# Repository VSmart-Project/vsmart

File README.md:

# Vsmart — Cloud-based Vehicle GPS Tracking and Management System (IoT)

> **Graduation Project** — Real-time GPS Tracking, Geofencing, Anti-theft protection, and instant intrusion alerts system, built entirely on AWS Serverless Cloud Architecture.

## Quick local start

From the `DATN` directory, start the configured local services with:

```bash
./start-system.sh
```

The script starts the backend (port 3001) and web dashboard (port 5173) by default.
Pass `--with-mobile` if you want to start the Expo mobile app as well.
Use `./start-system.sh --help` to view all available options. Press `Ctrl+C` or run `./stop-system.sh`
to stop all running services. Service logs are retained under `.runtime/logs/`.

---

## Table of Contents

1. [Project Overview](#1-project-overview)
2. [Source Code Directory Structure](#2-source-code-directory-structure)
3. [System Architecture](#3-system-architecture)
4. [AWS Services Utilized](#4-aws-services-utilized)
5. [System Workflows](#5-system-workflows)
6. [Deployment Guide](#6-deployment-guide)
   - [Step 1: System Prerequisites](#step-1-system-prerequisites)
   - [Step 2: Deploy AWS Infrastructure](#step-2-deploy-aws-infrastructure)
   - [Step 3: Configure & Run Backend](#step-3-configure--run-backend)
   - [Step 4: Configure & Run Frontend Web Dashboard](#step-4-configure--run-frontend-web-dashboard)
   - [Step 5: Configure & Run Mobile App](#step-5-configure--run-mobile-app)
   - [Step 6: GPS Simulation & End-to-End Testing](#step-6-gps-simulation--end-to-end-testing)
7. [API Reference](#7-api-reference)
8. [Troubleshooting & FAQ](#8-troubleshooting--faq)
9. [Local-First & ngrok Webhook Workflow](#9-local-first--ngrok-webhook-workflow)
10. [Technology Stack](#10-technology-stack)
11. [References](#11-references)

---

## 1. Project Overview

### Problem Statement

Traditional fleet management systems usually require dedicated physical servers, resulting in high operational costs, maintenance overhead, and poor scalability. The **Vsmart** project solves these issues by leveraging a modern **Serverless Event-Driven Architecture** on AWS, eliminating server management while ensuring high availability, lower latency, and pay-as-you-go cost-efficiency.

### Key Features

| Feature | Description |
|---|---|
| **Real-time GPS Tracking** | Visualizes live vehicle locations on high-performance vector maps |
| **Geofencing** | Custom virtual boundaries (Polygon/Circle) with instant entrance/exit notifications |
| **Anti-theft Security** | Automatic 2-meter radius geofencing around parked vehicles with instant push/email alerts on breach |
| **Multi-platform** | Synchronized Web Dashboard (React) + Mobile App (React Native/Expo) |
| **Identity & Authentication** | Secure user registration/sign-in using Amazon Cognito + JWT verification |
| **Position History** | Replays past vehicle travel routes along a timeline with detailed logs |
| **Serverless & Scalable** | Entire pipeline scale dynamically based on ingestion load, keeping maintenance near zero |
| **Infrastructure as Code (IaC)** | Deploys 30+ AWS resources using a single command via AWS CloudFormation/SAM |

---

## 2. Source Code Directory Structure

The project is structured into **4 independent modules**, enabling isolated development and deployment:

```
7-DATN/
│
├── vsmart-infrastructure/   ← AWS Serverless Infrastructure (IaC)
│   ├── template.yml                             # Primary SAM Template (30+ AWS resources)
│   ├── packaged.yml                             # Packaged Template containing S3 URIs
│   └── lambda/                                  # Serverless Functions (Python 3.12)
│       ├── iot-message-processor/               #   → Parses MQTT packets & updates ALS Tracker
│       ├── geofence-event-consumer/             #   → Processes Geofence breach events from SQS
│       ├── realtime-event-publisher/            #   → Publishes real-time events to clients via IoT Core
│       └── offline-detector/                    #   → Cron job identifying offline devices (every 1min)
│
├── vsmart-backend/          ← Node.js REST API & Socket.io Proxy
│   ├── index.js                                 # Entry point (Express server & Socket.io, port 3001)
│   ├── src/
│   │   ├── config/
│   │   │   ├── aws.js                           #   AWS SDK clients configuration
│   │   │   ├── constants.js                     #   Global constants & thresholds
│   │   │   ├── realtime.js                      #   Real-time telemetry flags
│   │   │   ├── realtimeEventSchema.js           #   Real-time event validations
│   │   │   └── swagger.js                       #   Swagger/OpenAPI UI config
│   │   ├── controllers/
│   │   │   ├── deviceController.js              #   CRUD operations & location metadata merging
│   │   │   ├── authController.js                #   Cognito user auth controller
│   │   │   └── antitheftController.js           #   Anti-theft activation and status
│   │   ├── routes/
│   │   │   ├── devices.js                       #   /api/devices endpoints
│   │   │   ├── auth.js                          #   /api/auth endpoints
│   │   │   └── antitheft.js                     #   /api/antitheft endpoints
│   │   ├── services/
│   │   │   ├── dynamoService.js                 #   DynamoDB wrapper
│   │   │   ├── locationService.js               #   Amazon Location Service wrapper
│   │   │   ├── snsService.js                    #   SNS SMS/Email notifications
│   │   │   ├── antitheftWorker.js               #   Parked vehicle monitor thread (15s interval)
│   │   │   └── geoUtils.js                      #   Distance calculations (Turf.js)
│   │   └── middleware/
│   │       ├── auth.js                          #   Cognito ID Token JWT verifier
│   │       └── errorHandler.js                  #   Global error catcher
│   └── scripts/
│       ├── interactive-move.js                  #   Interactive GPS Simulator (MQTT → IoT Core)
│       ├── move-device.js                       #   Single device route simulator
│       └── backfill-device-owners.js            #   Owner backfill utility script
│
├── vsmart-web/             ← Web Client (React 19 + Vite 8)
│   ├── index.html                               # HTML Entry
│   ├── vite.config.js                           # Vite bundler config (port 5173)
│   ├── tailwind.config.js                       # TailwindCSS styles configuration
│   └── src/
│       ├── App.jsx                              # Router, auth checks, and Socket.io client
│       ├── configuration.js                     # Local AWS config mapping
│       ├── components/
│       │   ├── auth/                            #   Sign-in, sign-up, and confirmation forms
│       │   ├── map/                             #   MapLibre GL map view & draw controllers
│       │   ├── devices/                         #   Vehicle list, details, and forms
│       │   ├── geofences/                       #   Geofencing controls & drawers
│       │   └── layout/                          #   Sidebar and Header layouts
│       ├── hooks/                               #   Custom React hooks (useDeviceManager, etc.)
│       ├── api/                                 #   Fetch-based REST client
│       └── utils/                               #   AWS Identity Pool credentials resolver
│
└── vsmart-mobile/                               ← Mobile Client (React Native + Expo SDK 54)
    ├── app.json                                 # Expo configuration file
    ├── app/                                     # File-based navigation screens
    │   ├── _layout.jsx                          #   Root provider layout
    │   ├── login.jsx                            #   Login screen
    │   ├── onboarding.jsx                       #   Onboarding flow
    │   ├── map.jsx                              #   Full screen map tracking view
    │   ├── scan.jsx                             #   Camera QR/Barcode scanner
    │   └── (tabs)/                              #   Tab navigator (Home, Devices, Settings)
    └── src/
        ├── configuration.js                     #   Mobile AWS configuration constants
        ├── contexts/                            #   Global contexts (DeviceDataContext, etc.)
        └── utils/                               #   Cognito authentication & AWS SDK helpers
```

---

## 3. System Architecture

The system utilizes an **Event-Driven Serverless Ingestion Pipeline** on AWS coupled with a **Node.js WebSockets Proxy** to handle live telemetry feeds with millisecond latency:

```mermaid
%%{init: {'theme': 'base', 'themeVariables': { 'fontFamily': 'Inter, sans-serif', 'fontSize': '13px', 'primaryColor': '#4f46e5', 'primaryTextColor': '#ffffff', 'primaryBorderColor': '#4338ca', 'lineColor': '#64748b', 'secondaryColor': '#f8fafc', 'tertiaryColor': '#ffffff' }}}%%
graph TB
    subgraph Clients ["Client Applications"]
        Web["Web Dashboard (React + Vite)"]
        Mobile["Mobile App (React Native + Expo)"]
    end

    subgraph Backend ["Backend Proxy (Node.js & Express)"]
        Express["Express Server (Port 3001)"]
        SocketServer["Socket.io Server (WebSocket Broker)"]
        AntitheftWorker["Anti-theft Worker (Interval: 15s)"]
    end

    subgraph AWSCloud ["AWS Serverless Cloud Infrastructure"]
        IoTCore["AWS IoT Core (MQTT Broker)"]
        LambdaIngest["Lambda: IoTMessageProcessor"]
        LambdaGeofence["Lambda: GeofenceEventConsumer"]
        LambdaOffline["Lambda: OfflineDetector (Cron: 1min)"]
        
        subgraph Databases ["AWS Databases"]
            DynamoDevices[("DynamoDB: DevicesTable")]
            DynamoState[("DynamoDB: DeviceStateTable")]
        end
        
        subgraph LocationServices ["AWS Location Services"]
            ALSMap["Map: Vsmart-Map"]
            ALSTracker["Tracker: Vsmart-Tracker"]
            ALSCollection["Collection: GeofenceCollection"]
        end
        
        EventBridge["Amazon EventBridge"]
        SQSQueue["Amazon SQS (Geofence Alerts)"]
        SNSTopic["Amazon SNS (Email Alerts)"]
        Cognito["Amazon Cognito (User & Identity Pools)"]
    end

    %% Connections
    Web & Mobile <-->|"1. REST API Requests (Cognito JWT)"| Express
    Web & Mobile <-->|"2. Socket.io WebSockets"| SocketServer
    Web & Mobile -->|"3. Vector Map Tiles Fetch"| ALSMap
    Web & Mobile -->|"4. Credentials Exchange"| Cognito

    %% Ingestion
    Simulator["GPS Device / Simulator"] -->|"5. Publish Location (MQTT)"| IoTCore
    IoTCore -->|"6. Trigger Rule"| LambdaIngest
    
    LambdaIngest -->|"7a. Log coordinate history"| ALSTracker
    LambdaIngest -->|"7b. Save latest state"| DynamoState
    LambdaIngest -->|"7c. HTTP POST Webhook"| Express
    
    %% Geofence Transitions
    ALSTracker -->|"8. Evaluate transitions"| ALSCollection
    ALSCollection -->|"9. ENTER/EXIT Event"| EventBridge
    EventBridge -->|"10. Queue message"| SQSQueue
    SQSQueue -->|"11. Poll batch"| LambdaGeofence
    LambdaGeofence -->|"12. HTTP POST Webhook (Alert)"| Express

    %% Anti-theft Guard
    AntitheftWorker -->|"13. Query coordinates"| DynamoState & ALSTracker
    AntitheftWorker -->|"14. Trigger Alert (Breach)"| SNSTopic

    %% Cron Tasks
    EventBridge -->|"15. Trigger Cron"| LambdaOffline
    LambdaOffline -->|"16. Mark Offline (>120s)"| DynamoState
    LambdaOffline -->|"17. HTTP POST Webhook (Status)"| Express

    %% Webhook forwarding to sockets
    Express -->|"18. Forward event payload"| SocketServer

    %% Styling classes
    style Web fill:#e0f2fe,stroke:#38bdf8,stroke-width:2px,color:#0f172a
    style Mobile fill:#e0f2fe,stroke:#38bdf8,stroke-width:2px,color:#0f172a
    style Express fill:#faf5ff,stroke:#c084fc,stroke-width:2px,color:#0f172a
    style SocketServer fill:#faf5ff,stroke:#c084fc,stroke-width:2px,color:#0f172a
    style AntitheftWorker fill:#faf5ff,stroke:#c084fc,stroke-width:2px,color:#0f172a
    style IoTCore fill:#fff7ed,stroke:#fdba74,stroke-width:2px,color:#0f172a
    style LambdaIngest fill:#fff7ed,stroke:#fdba74,stroke-width:2px,color:#0f172a
    style LambdaGeofence fill:#fff7ed,stroke:#fdba74,stroke-width:2px,color:#0f172a
    style LambdaOffline fill:#fff7ed,stroke:#fdba74,stroke-width:2px,color:#0f172a
    style EventBridge fill:#fff7ed,stroke:#fdba74,stroke-width:2px,color:#0f172a
    style SQSQueue fill:#fff7ed,stroke:#fdba74,stroke-width:2px,color:#0f172a
    style SNSTopic fill:#fff7ed,stroke:#fdba74,stroke-width:2px,color:#0f172a
    style Cognito fill:#fff7ed,stroke:#fdba74,stroke-width:2px,color:#0f172a
    style DynamoDevices fill:#f0fdf4,stroke:#86efac,stroke-width:2px,color:#0f172a
    style DynamoState fill:#f0fdf4,stroke:#86efac,stroke-width:2px,color:#0f172a
    style ALSMap fill:#f0fdfa,stroke:#5eead4,stroke-width:2px,color:#0f172a
    style ALSTracker fill:#f0fdfa,stroke:#5eead4,stroke-width:2px,color:#0f172a
    style ALSCollection fill:#f0fdfa,stroke:#5eead4,stroke-width:2px,color:#0f172a
```

### Architectural Design Principles

| Principle | Description |
|---|---|
| **Separation of Concerns** | Decouples IoT telemetry ingestion from application API layers to prevent system crashes on high device activity. |
| **Event-Driven & Serverless** | Coordinates flow automatically through EventBridge, SQS, and Lambda, providing cost-efficiency and horizontal scaling. |
| **Dual Data Pipeline** | Integrates low-cost NoSQL storage (DynamoDB for metadata) with specialized geo-caching databases (Amazon Location Tracker for spatial coordinates). |
| **WebSockets API Gateway Proxy** | Connects clients via lightweight Socket.io WebSockets instead of direct AWS MQTT. The backend exposes a secure `/api/realtime/event` webhook called by AWS Lambda. |
| **Cognito-Federated Identity** | Uses Amazon Cognito User Pools for authorization. The client exchanges JWT tokens for AWS temporary credentials via Cognito Identity Pools to read map vector tiles directly. |

---

## 4. AWS Services Utilized

### Core Services

| Service | Resource Name | Purpose |
|---|---|---|
| **Amazon Location Service** | `Vsmart-Map` | Renders map vector tiles (Esri Navigation style) |
| | `Vsmart-Tracker` | Caches coordinates history, applies `DistanceBased` filtering |
| | `Vsmart-GeofenceCollection` | Stores geofence boundary coordinates |
| **AWS IoT Core** | Rule: `UpdateLocationTracker` | Receives incoming MQTT telemetry and routes payload to Lambda |
| **Amazon DynamoDB** | `Vsmart-Devices` | Device profiles database (name, license plate, status) |
| | `Vsmart-DeviceState` | Live runtime state database (online flag, last seen timestamp, anti-theft trigger) |
| **Amazon Cognito** | `Vsmart-UserPool` | Secure registration and login gateway |

### Supporting Services

| Service | Resource Name | Purpose |
|---|---|---|
| **AWS Lambda** | `IoTMessageProcessor` | Validates telemetry ➔ updates location ➔ calls Backend Webhook |
| | `GeofenceEventConsumer` | Handles geofence breaches ➔ calls Backend Webhook |
| | `OfflineDetector` | Queries the online-state index and identifies offline vehicles (>120s) |
| **Amazon EventBridge** | `GeofenceEventRule` | Captures geofence breach notifications ➔ routes to SQS |
| | `OfflineDetectorSchedule` | Generates cron triggers every minute |
| **Amazon SQS** | `GeofenceEvents` | Queues geofence breach events for batch consumption |
| **Amazon SNS** | `AntitheftAlerts` | Dispatches warning emails to owners on anti-theft breaches |
| | `IoTErrors` | Emails administrators on processing failures |
| **CloudFormation** | `Vsmart-UnifiedStack` | Deploys the entire backend cloud infrastructure as code |

---

## 5. System Workflows

### A. Location Telemetry Pipeline — GPS → Cloud → Clients

Updates vehicle markers on the map within milliseconds of receiving a new GPS coordinate:

```mermaid
%%{init: {'theme': 'base', 'themeVariables': { 'fontFamily': 'Inter, sans-serif', 'fontSize': '12px', 'primaryColor': '#4f46e5', 'primaryTextColor': '#ffffff', 'lineColor': '#64748b' }}}%%
sequenceDiagram
    autonumber
    participant Device as 🛰️ GPS Device
    participant IoT as 📡 AWS IoT Core
    participant Ingest as ⚡ Lambda: IoTMessageProcessor
    participant ALS as 📍 AWS Location Tracker
    participant Dynamo as 🗄️ DynamoDB (DeviceState)
    participant Backend as 🔧 Backend Express
    participant WebSockets as 🔌 Socket.io Server
    participant UI as 💻 Client Map UI

    Device->>IoT: Publish MQTT payload (location topic)
    IoT->>Ingest: Trigger Lambda with payload
    activate Ingest
    Ingest->>ALS: batch_update_device_position(Coordinates)
    Ingest->>Dynamo: Update state (isOnline=true, lastSeenAt, coordinates)
    Ingest->>Backend: HTTP POST /api/realtime/event (with API Key)
    deactivate Ingest
    activate Backend
    Backend->>WebSockets: Emit 'realtime-event'
    deactivate Backend
    WebSockets-->>UI: Push position data via WebSocket connection
    UI->>UI: Re-render map marker dynamically (smooth translation)
```

---

### B. Device Registration & Retrieval Workflow

Fetches registered devices, resolving metadata and coordinates from distinct databases:

```mermaid
%%{init: {'theme': 'base', 'themeVariables': { 'fontFamily': 'Inter, sans-serif', 'fontSize': '12px', 'primaryColor': '#4f46e5', 'primaryTextColor': '#ffffff', 'lineColor': '#64748b' }}}%%
sequenceDiagram
    autonumber
    participant UI as 💻 Web/Mobile Client
    participant Backend as 🔧 Backend Express
    participant Cognito as 🔐 AWS Cognito
    participant Dynamo as 🗄️ DynamoDB (DevicesTable)
    participant ALS as 📍 AWS Location Tracker

    UI->>Backend: GET /api/devices (Header: Bearer JWT)
    activate Backend
    Backend->>Cognito: Verify JWT signature & expiry
    Cognito-->>Backend: Verification success
    Backend->>Dynamo: Scan/Query device metadata by ownerUserId
    Dynamo-->>Backend: Return metadata (name, plate, type, antitheft)
    Backend->>ALS: ListDevicePositions (Fetch last coordinates)
    ALS-->>Backend: Return positions & timestamps
    Backend->>Backend: Merge metadata & position by deviceId
    Backend->>Backend: Calculate isOnline (sampleTime < 2 mins)
    Backend-->>UI: Return JSON Response
    deactivate Backend
```

---

### C. Geofencing Warning Pipeline

Monitors boundary crossings and alerts clients in real-time:

```mermaid
%%{init: {'theme': 'base', 'themeVariables': { 'fontFamily': 'Inter, sans-serif', 'fontSize': '12px', 'primaryColor': '#4f46e5', 'primaryTextColor': '#ffffff', 'lineColor': '#64748b' }}}%%
sequenceDiagram
    autonumber
    participant UI as 💻 Web Dashboard
    participant Cognito as 🔐 Cognito Identity Pool
    participant ALS as 📍 AWS Location (GeofenceCollection)
    participant EventBridge as 📅 AWS EventBridge
    participant SQS as 📊 Amazon SQS Queue
    participant Consumer as ⚡ Lambda: GeofenceEventConsumer
    participant Backend as 🔧 Backend Express
    participant WebSockets as 🔌 Socket.io Server
    participant AlertUI as 📱 Client App (Toast/Notification)

    UI->>Cognito: Request temporary credentials
    Cognito-->>UI: Return Access & Secret Keys
    UI->>ALS: Direct PUT /geofences (GeoJSON Polygon/Circle)
    Note over ALS: ALS Tracker evaluates coordinates against Geofences
    ALS->>EventBridge: Publish event on ENTER/EXIT transition
    EventBridge->>SQS: Push event to Queue
    SQS->>Consumer: Trigger Lambda with batch of events
    activate Consumer
    Consumer->>Backend: HTTP POST /api/realtime/event (Alert payload)
    deactivate Consumer
    activate Backend
    Backend->>WebSockets: Broadcast alert to user's room
    deactivate Backend
    WebSockets-->>AlertUI: Push geofence alert event
    AlertUI->>AlertUI: Display Toast Alert & Play Alarm Sound
```

---

### D. Anti-theft Protection Workflow

Secures parked vehicles using automated, short-range geofencing:

```mermaid
%%{init: {'theme': 'base', 'themeVariables': { 'fontFamily': 'Inter, sans-serif', 'fontSize': '12px', 'primaryColor': '#4f46e5', 'primaryTextColor': '#ffffff', 'lineColor': '#64748b' }}}%%
sequenceDiagram
    autonumber
    participant UI as 📱 Web/Mobile Client
    participant Backend as 🔧 Backend Express
    participant ALS as 📍 AWS Location (GeofenceCollection)
    participant Dynamo as 🗄️ DynamoDB (DeviceStateTable)
    participant Worker as 🛡️ Anti-theft Worker (Interval: 15s)
    participant SNS as 📬 Amazon SNS
    participant Email as 📧 Owner's Email

    UI->>Backend: POST /api/antitheft/:deviceId/enable
    activate Backend
    Backend->>ALS: Get current position of device
    Backend->>ALS: PutGeofence (Create R=2m circle around coordinates)
    Backend->>Dynamo: Update state (antitheftEnabled = true, geofenceId = ...)
    Backend-->>UI: Return Success
    deactivate Backend

    loop Every 15 seconds
        Worker->>Dynamo: Scan devices where antitheftEnabled == true
        Dynamo-->>Worker: Return target devices
        Worker->>ALS: Get current coordinates
        ALS-->>Worker: Return current coordinates
        Worker->>Worker: Check if distance from anchor coordinates > 2m
        alt Distance > 2 meters (Breach detected!)
            Worker->>SNS: Publish Alert message to topic
            SNS-->>Email: Deliver "WARNING: Vehicle breached protection zone!"
            Worker->>Dynamo: Disable anti-theft (prevent alert spamming)
        end
    end
```

---

### E. Silent Offline Detection Workflow

Automatically detects lost network or GPS connection:

```mermaid
%%{init: {'theme': 'base', 'themeVariables': { 'fontFamily': 'Inter, sans-serif', 'fontSize': '12px', 'primaryColor': '#4f46e5', 'primaryTextColor': '#ffffff', 'lineColor': '#64748b' }}}%%
sequenceDiagram
    autonumber
    participant EventBridge as 📅 EventBridge Cron (rate: 1min)
    participant Detector as ⚡ Lambda: OfflineDetector
    participant Dynamo as 🗄️ DynamoDB (DeviceStateTable)
    participant Backend as 🔧 Backend Express
    participant WebSockets as 🔌 Socket.io Server
    participant UI as 📱 Client App (List View)

    EventBridge->>Detector: Trigger Lambda
    activate Detector
    Detector->>Dynamo: Scan online devices (isOnline == true)
    Dynamo-->>Detector: Return online devices list
    loop Each Device
        Detector->>Detector: Check if (now - lastSeen) > 120 seconds
        alt Threshold exceeded (Offline!)
            Detector->>Dynamo: Update state (isOnline = false, isOnlineStr = "false")
            Detector->>Backend: HTTP POST /api/realtime/event (device.status.offline)
        end
    end
    deactivate Detector
    activate Backend
    Backend->>WebSockets: Broadcast offline status to user room
    deactivate Backend
    WebSockets-->>UI: Push offline event
    UI->>UI: Gray out device icon & mark badge 'offline'
```

---

## 6. Deployment Guide

### Step 1: System Prerequisites

Ensure you have the following installed on your development machine:

| Tool | Version | Description |
|---|---|---|
| **Node.js** | v20+ LTS | JavaScript Runtime for Backend and Frontend |
| **npm** | v10+ | Package manager |
| **AWS CLI** | v2 | Configured with `aws configure` |
| **AWS Account** | — | Requires permissions for: CloudFormation, IAM, Lambda, Location Service, IoT Core, Cognito, DynamoDB, SNS, SQS, EventBridge |
| **ngrok** | Latest | Used to route local Node.js server for AWS Lambda webhooks |

#### Configure AWS CLI

```bash
aws configure
# AWS Access Key ID: AKIA...
# AWS Secret Access Key: ...
# Default region name: ap-southeast-1
# Default output format: json
```

---

### Step 2: Deploy AWS Infrastructure

The AWS Cloud Services are declared as Infrastructure as Code in `template.yml` under `vsmart-infrastructure/`.

#### 2.1. Clone the Repository
```bash
git clone https://github.com/Tracking-Data-Streaming/.github.git
cd 7-DATN
```

#### 2.2. Create an S3 Bucket for Lambda Artifacts
AWS CloudFormation requires a globally unique S3 bucket to package Lambda code before deployment:
```bash
aws s3 mb s3://vsmart-tracking-artifacts-by-tranvix0910 --region ap-southeast-1
```

#### 2.3. Package the Template
Zip the Lambda code, upload it to S3, and generate the template containing absolute S3 URIs:
```bash
cd vsmart-infrastructure
aws cloudformation package \
  --template-file template.yml \
  --s3-bucket vsmart-tracking-artifacts-by-tranvix0910 \
  --output-template-file packaged.yml \
  --region ap-southeast-1
```

#### 2.4. Expose the Local Webhook Port via ngrok
To receive real-time telemetry events from AWS Lambda on your local machine, start an ngrok tunnel pointing to your local Express server (port 3001):
```bash
ngrok http 3001
```
Copy the generated HTTPS Forwarding URL ending with `.dev` (e.g. `https://abc-123.ngrok-free.dev`). Your Webhook URL will be:
`https://abc-123.ngrok-free.dev/api/realtime/event`

#### 2.5. Deploy the Stack
Deploy the CloudFormation template, passing your email and your ngrok webhook URL:
```bash
aws cloudformation deploy \
  --template-file packaged.yml \
  --stack-name Vsmart-UnifiedStack \
  --capabilities CAPABILITY_NAMED_IAM \
  --parameter-overrides AlertEmail="tranvix.work@gmail.com" BackendWebhookUrl="https://aggregate-jelly-president.ngrok-free.dev/api/realtime/event" \
  --region ap-southeast-1
```
*(Replace `https://abc-123.ngrok-free.dev` with your actual active ngrok URL).*

> 💡 **Tip:** If your ngrok URL changes after restarting ngrok, you do **not** need to redeploy the whole CloudFormation stack. You can quickly update the 3 Lambda functions via AWS CLI:
> ```bash
> export NGROK_URL="https://YOUR_NEW_NGROK.ngrok-free.dev/api/realtime/event"
>
> for fn in $(aws lambda list-functions --region ap-southeast-1 --query "Functions[?starts_with(FunctionName, 'Vsmart-UnifiedStack')].FunctionName" --output text); do
>   aws lambda update-function-configuration --function-name "$fn" \
>     --environment "Variables={$(aws lambda get-function-configuration --function-name "$fn" --region ap-southeast-1 --query "Environment.Variables" --output json | jq -r 'to_entries | map("\(.key)=\(.value)") | join(",")' | sed "s|BACKEND_WEBHOOK_URL=[^,]*|BACKEND_WEBHOOK_URL=$NGROK_URL|")}" \
>     --region ap-southeast-1 >/dev/null 2>&1
> done
> ```

#### 2.6. Confirm SNS Subscription
AWS will send a validation email to the configured `AlertEmail`. **Open the email and click "Confirm subscription"** to enable anti-theft emails.

#### 2.7. Extract CloudFormation Outputs
Export the resource IDs needed to configure your client applications:
```bash
aws cloudformation describe-stacks \
  --stack-name Vsmart-UnifiedStack \
  --query "Stacks[0].Outputs" \
  --output table \
  --region ap-southeast-1
```

#### 2.8. Create Location Service API Key (Mandatory)
AWS Location Service maps require an API key for map rendering, which must be created manually:

```bash
ACCOUNT_ID=$(aws sts get-caller-identity --query Account --output text)

aws location create-key \
  --key-name Vsmart-MapApiKey \
  --restrictions "{
    \"AllowActions\": [\"geo:GetMapStyleDescriptor\",\"geo:GetMapGlyphs\",\"geo:GetMapSprites\",\"geo:GetMapTile\"],
    \"AllowResources\": [\"arn:aws:geo:ap-southeast-1:${ACCOUNT_ID}:map/Vsmart-Map\"]
  }" \
  --no-expiry \
  --region ap-southeast-1 \
  --query "Key" --output text
```

---

### Step 3: Configure & Run Backend

#### 3.1. Install Dependencies
```bash
cd ../vsmart-backend
npm install
```

#### 3.2. Configure Environment Variables (`.env`)
```bash
cp .env.example .env
```
Open `.env` and fill in the output parameters:
```env
PORT=3001
NODE_ENV=development
AWS_REGION=ap-southeast-1
AWS_PROFILE=default # Local development only; use an IAM role in production
DYNAMODB_DEVICES_TABLE=Vsmart-Devices
LOCATION_TRACKER_NAME=Vsmart-Tracker
LOCATION_GEOFENCE_COLLECTION=Vsmart-GeofenceCollection
SNS_ANTITHEFT_TOPIC_ARN=arn:aws:sns:ap-southeast-1:xxxxxx:Vsmart-AntitheftAlerts
CORS_ORIGIN=*
COGNITO_USER_POOL_ID=ap-southeast-1_xxxxxx
COGNITO_CLIENT_ID=xxxxxx
REALTIME_WEBHOOK_KEY=vsmart_secret_telemetry_key
```

#### 3.3. Start the Server
```bash
npm start
```
*Successful log:* `🔌 Realtime: Socket.io server integrated and running`

---

### Step 4: Configure & Run Frontend Web Dashboard

#### 4.1. Install Dependencies
```bash
cd ../vsmart-web
npm install
```

#### 4.2. Configure Environment Variables (`.env`)
```bash
cp .env.example .env
```
Fill in the parameters in `.env`:
```env
VITE_BACKEND_URL=http://localhost:3001
VITE_AWS_REGION=ap-southeast-1
VITE_USER_POOL_ID=ap-southeast-1_xxxxxx
VITE_USER_POOL_CLIENT_ID=xxxxxx
VITE_MAP_API_KEY=v1.public.eyJ... # Map API Key generated in step 2.8
VITE_MAP_STYLE=Standard
VITE_MAP_COLOR_SCHEME=Light
VITE_GEOFENCE_COLLECTION=Vsmart-GeofenceCollection
```

#### 4.3. Start the Web App
```bash
npm run dev
```
Open `http://localhost:5173` on your browser.

---

### Step 5: Configure & Run Mobile App

#### 5.1. Install Dependencies
```bash
cd ../vsmart-mobile
npm install
```

#### 5.2. Configure Settings
Copy `.env.example` to `.env` and point the app to the backend (use a LAN URL for local devices and HTTPS for production):
```env
EXPO_PUBLIC_BACKEND_URL=http://192.168.1.xxx:3001
EXPO_PUBLIC_AWS_REGION=ap-southeast-1
EXPO_PUBLIC_USER_POOL_ID=ap-southeast-1_xxxxxx
EXPO_PUBLIC_USER_POOL_CLIENT_ID=xxxxxx
```

#### 5.3. Start the App
```bash
npm start
```
Scan the QR Code with the **Expo Go** application on your smartphone (connected to the same WiFi LAN).

---

### Step 6: GPS Simulation & End-to-End Testing

#### 6.1. Start the Simulator
Open a new terminal window inside `vsmart-backend` and run:
```bash
node scripts/interactive-move.js
```
#### 6.2. Simulate Route Movement
Type the following command at the prompt `📍 Command >` to begin sending GPS coordinate packages:
```bash
auto 10.8481 106.7864 30
```
On your browser, you will observe the vehicle marker moving smoothly on the map in real-time (2-second intervals).

---

## 7. API Reference

### Auth Endpoints (Public)

| Method | Endpoint | Description |
|---|---|---|
| `POST` | `/api/auth/register` | Signs up a new account (email & password) |
| `POST` | `/api/auth/confirm` | Confirms registration using OTP verification |
| `POST` | `/api/auth/login` | Authenticates user and returns JWT |
| `POST` | `/api/auth/resend-code` | Re-sends the verification code |

### Device Endpoints (Protected)

| Method | Endpoint | Description |
|---|---|---|
| `GET` | `/api/devices` | Returns registered device list merged with positions |
| `GET` | `/api/devices/:id` | Returns metadata details for a specific device |
| `GET` | `/api/devices/:id/history` | Returns coordinate path history for timeline routing |
| `POST` | `/api/devices` | Registers a new device |
| `PUT` | `/api/devices/:id` | Updates device metadata |
| `DELETE` | `/api/devices/:id` | Deletes a device and clear tracker logs |

### Anti-theft Endpoints (Protected)

| Method | Endpoint | Description |
|---|---|---|
| `POST` | `/api/antitheft/:deviceId/enable` | Activates protection (creates R=2m geofence) |
| `POST` | `/api/antitheft/:deviceId/disable` | Deactivates anti-theft (removes geofence) |

### Webhook & Diagnostics

| Method | Endpoint | Description |
|---|---|---|
| `POST` | `/api/realtime/event` | Endpoint receiving Lambda webhook signals (API Key protected) |
| `GET` | `/health` | Informs backend health status and active configuration |
| `GET` | `/api-docs` | Interactive Swagger API documentation |

---

## 8. Troubleshooting & FAQ

#### Lambda error: `Float types are not supported` in CloudWatch
* **Cause**: DynamoDB does not support native Python `float` types.
* **Solution**: The code has been updated to automatically cast floats to `decimal.Decimal` before saving coordinates in DynamoDB (`DeviceStateTable`).

#### Webhook errors: `HTTP Error 404: Not Found`
* **Cause**: Typo in the `BackendWebhookUrl` parameter or ngrok tunnel pointing to incorrect port.
* **Solution**: Ensure your ngrok tunnel is up and ends with `.dev`. Run `aws lambda get-function-configuration` to confirm `BACKEND_WEBHOOK_URL` matches your tunnel url exactly.

#### Map is blank or fails to load style
* **Cause**: Map API Key is incorrect, expired, or has improper resource constraints.
* **Solution**: Double-check `VITE_MAP_API_KEY` matches the key created in Step 2.8. Ensure the key restrictions grant allow actions on the map resource `Vsmart-Map`.

---

## 9. Local-First & ngrok Webhook Workflow

The entire system is designed to run **100% locally on your development machine** without requiring external cloud app hosts or VPS.

### 9.1. Local-First Architecture

```
[ GPS Device / Simulator ] ──► [ AWS IoT Core ] ──► [ AWS Lambda ]
                                                          │
                                                (Webhook via ngrok)
                                                          │
                                                          ▼
[ Local Browser / Mobile ] ◄─── [ Socket.io ] ◄─── [ Local Express (Port 3001) ]
```

1. **Local Express Server (Port 3001)**: Handles all REST API requests, database queries, and WebSocket broadcasting.
2. **ngrok Tunnel**: Creates a secure public tunnel to route AWS Lambda webhook calls back to your machine.
3. **Local Web App (Port 5173)**: Connects directly to `http://localhost:3001`.
4. **Local Mobile App (Port 8081)**: Connects to your computer's LAN IP (e.g. `http://192.168.1.x:3001`).

### 9.2. Daily Local Development Workflow

1. **Start ngrok (Tab 1):**
   ```bash
   ngrok http 3001
   ```
2. **Start the local services (Tab 2):**
   ```bash
   ./start-system.sh
   ```
3. **Run GPS Simulation (Tab 3):**
   ```bash
   cd vsmart-backend
   node scripts/interactive-move.js
   ```
4. **Stop everything when finished:**
   ```bash
   ./stop-system.sh
   # Or press Ctrl+C in Tab 2
   ```

---

## 10. Technology Stack

### Frontend & Mobile
* **React 19.2** & **Vite 8.0**
* **React Native v0.81** & **Expo SDK 54**
* **MapLibre GL JS** (Vector Tiles Rendering)
* **Tailwind CSS** (Utility-first Styling)
* **AWS Amplify (Auth v6)**
* **Socket.io Client** (WebSocket Telemetry)

### Backend Services
* **Node.js v20** & **Express.js**
* **Socket.io Server**
* **AWS SDK for JS (v3)**
* **Swagger OpenAPI UI**

### Cloud Infrastructure
* **AWS CloudFormation / SAM**
* **Amazon Location Service (Maps, Tracker, Geofences)**
* **AWS IoT Core**
* **Amazon DynamoDB**
* **Amazon EventBridge & SQS & SNS**

---

## 11. References

* [Amazon Location Service Developer Guide](https://docs.aws.amazon.com/location/)
* [AWS IoT Core Developer Guide](https://docs.aws.amazon.com/iot/)
* [Socket.io Official Documentation](https://socket.io/docs/v4/)
* [Expo Router Navigation Guidelines](https://docs.expo.dev/router/introduction/)

---

## LICENSE
This project is licensed under the **MIT License** — see the [LICENSE](LICENSE) file for details.

---

## Thesis Metadata

| Parameter | Detail |
|---|---|
| **Thesis Title** | Cloud-based IoT Fleet Management and Real-time Tracking System |
| **Academic Level** | Graduation Thesis (Bachelor of Engineering) |
| **Architecture** | Serverless Ingestion + Node.js WebSockets Proxy |
| **Cloud Provider** | Amazon Web Services (AWS) |
| **Default Region** | `ap-southeast-1` (Singapore) |

---
<div align="center">
  <b>Happy Tracking!</b>
</div>

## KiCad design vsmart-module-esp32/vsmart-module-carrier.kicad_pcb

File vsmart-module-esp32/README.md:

# VSmart module carrier — ESP32-DevKitC (board 2)

Carrier lắp tay cho ESP32-DevKitC 38 chân + A7680C 4G + GPS NEO-7M (GY-GPSU3) + MPU6050. Board 105.1 × 82.1 mm, 2 lớp, mọi module cắm header.

## Rev C — trạng thái gia công (2026-08-30)

| Kiểm tra | Kết quả |
|---|---|
| DRC (`kicad-cli` 10.0.5, severity-all) | **0 vi phạm** (trước: 75) |
| Pad chưa nối / đối chiếu schematic ↔ PCB | **0 / 0** |
| Bộ gerber (`analyze_gerbers`) | **0 phát hiện**, đủ 7/7 lớp |
| Cross-domain | **0 phát hiện** |
| EMC risk score | 71.5/100 |
| Via | 294 (284 khâu GND + 4 hồi dòng + 1 chuyển lớp +3V3) |
| Lỗ khoan | 364 PTH + 5 NPTH, nhỏ nhất 0.3 mm |

Nộp xưởng: `manufacturing/vsmart-module-carrier-fab.zip` — 10 file phẳng.

## Đã sửa trong đợt này

### Điện áp — ba lỗi giống hệt board ESP32-S3

| Hạng mục | Trước | Sau |
|---|---|---|
| Net cấp U4 | `+4V_SIM` (4.0 V) | `+5V_SIM` (5 V 2 A) |
| Nguồn U3 (GPS) | `+5V` | `+3V3` |
| C1 | 1000 µF / 6.3 V | **1000 µF / 16 V** |

Ở 5 V thì tụ 6.3 V chỉ còn dư 21 % — quá sát cho tụ hoá tải xung 2 A.
Dùng loại **16 V, thân Ø10 mm** (footprint giữ nguyên).

### Đường mạch mới cho +3V3

Bỏ nhánh `+5V` chạy sang U3, **tái sử dụng hành lang B.Cu ở y ≈ 42.09** làm
đường `+3V3`, nối vào bằng nhánh mới qua cột trống x = 37.5:

```
U1.3V3 ─ B.Cu ─ (37.5, 59.22) ─ (37.5, 44.6) ─ (62.92, 44.6) ─ (62.92, 42.09) ─ … ─ U3.1
```

Không thể rẽ thẳng tại x = 62.92 vì `I2C_SCL` cắt ngang ở đó; cột x = 37.5 là
chỗ duy nhất trống ≥ 2 mm trên **cả hai mặt**.

### 75 → 0 vi phạm DRC

| Lỗi | Số | Nguyên nhân | Cách sửa |
|---|---|---|---|
| `clearance` | 18 | Netclass `POWER_SIM` cần hở 0.3 mm, vùng đồng đổ với 0.25 mm | Đặt zone clearance = 0.3 |
| `text_height` | 44 | Nhãn chân U1 (0.7 mm) và U4 (0.762 mm) dưới ngưỡng 0.8 | Nâng lên 0.85 |
| `lib_footprint_issues` | 7 | `fp-lib-table` trỏ sai thư mục dự án | Đổi sang `${KIPRJMOD}` |
| `silk_over_copper` | 6 | Silk U3 phủ chính chân nó; text B.Silk đè pad J1 | Thu mép silk, dời text |

Phát sinh và xử lý tiếp: nhãn chân U4 sau khi phóng to chạm pad → dịch trái
1.2 mm; footprint lỗ vít thay bằng bản thư viện chuẩn (mở mask 3.2 mm thay vì
6 mm hở đồng dưới đầu vít) → lộ ra **courtyard MH3 chồng U1 0.02 mm**, đã dời
MH3 và MH4 xuống y = 98.5 để giữ thẳng hàng.

### Bỏ C2 (100 nF gốm 0805)

Đo đường thật: C2 cách chân VCC của U4 **25 mm**. Với ~20 nH nối tiếp, tần số
tự cộng hưởng tụt về ~3.5 MHz — không còn làm được việc lọc cao tần. Bỏ để
thống nhất với board ESP32-S3 (tụ gốm dán khó hàn tay). Nếu modem reset khi
phát, hàn một tụ 104 thẳng lên chân VCC/GND của header U4.

### Silk

`+5V 1A` / `GND` cạnh J1, `+5V 2A` / `GND` cạnh J2 (mỗi nhãn thẳng hàng với
chân của nó), `SIM 5V 2A` cạnh U4, `GPS VCC=3V3` cạnh U3, `VSMART CARRIER REV C`
mặt sau.

## Đổi module GPS sang GY-GPSU3 (2026-08-30, cùng ngày)

Board này trước dùng **Keyestudio KS0319** (5 chân, thân 53 mm) trong khi board
ESP32-S3 đã dùng **GY-GPSU3** (4 chân, thân 25 mm). Nay đã thống nhất.

| | KS0319 | GY-GPSU3 |
|---|---|---|
| Chân | 5 (có PPS) | **4 (không PPS)** |
| Thân | 53 × 26 mm | **25 × 25 mm** |
| U3.1 | VCC | VCC |
| U3.2 | GND | **RXD** |
| U3.3 | TXD | TXD |
| U3.4 | RXD | **GND** |
| U3.5 | PPS | — |

**Hệ quả: net `GPS_PPS` bị bỏ hẳn.** GY-GPSU3 không có chân xung giây, nên
`U1.5 (GPIO34)` nay để trống và đã được đánh dấu no-connect. Nếu firmware của
bạn có dùng PPS để đồng bộ thời gian, **phải bỏ phần đó** — hoặc lấy thời gian
từ chuỗi NMEA (độ chính xác ~100 ms thay vì ~10 ns).

Ánh xạ chân đảo hoàn toàn nên phải đi lại 4 đường:

```
+3V3    hành lang B.Cu → via (118, 42.09) → F.Cu → U3.1 (122, 33.19)
GPS_TX  B.Cu y=34.46 → (118, 35.73) → U3.2 (122, 35.73)
GPS_RX  B.Cu y=41.03 → (116.74, 38.27) → U3.3 (122, 38.27)
GND     F.Cu trục dọc x=120.35 → U3.4 (122, 40.81)
```

`+3V3` phải nhảy sang F.Cu bằng via vì nó tới từ làn dưới cùng (y = 42.09)
nhưng chân đích lại nằm trên cùng (y = 33.19) — cắt qua cả `GPS_RX` và
`GPS_TX` nếu đi cùng lớp.

Một via khâu GND tại (120.45, 35.45) bị đường `GPS_TX` mới chạm vào và bị hút
sang net đó — đã phát hiện qua DRC (`via_dangling`) và xoá.

**Cơ hội chưa khai thác:** module mới nhỏ hơn 28 mm, giải phóng dải x = 69…99.
Nếu bố trí lại U3/U4/C1 thì có thể thu board xuống ≤ 100 mm để lọt bậc giá rẻ
(xem `DFM-001`). Chưa làm vì cần đi lại phần lớn đường mạch.

## Cây nguồn

| Rail | Đường đi | Bề rộng |
|---|---|---|
| `+5V` | J1 → C3 (470 µF/10 V) → U1.19 | 1.0 mm |
| `+5V_SIM` | J2 → C1 (1000 µF/16 V) → U4.8 | 2.0 mm |
| `+3V3` | U1.1 (ngõ ra LDO AMS1117) → U2.1 + U3.1 | 0.5–1.0 mm |
| `GND` | đổ đồng kín 2 mặt + 285 via khâu | — |

LDO 3.3 V trên DevKitC là **AMS1117-3.3 (~800 mA–1 A)** — dư sức gánh thêm GPS
(~50–80 mA). Đây là khác biệt lớn so với board ESP32-S3 SuperMini, nơi LDO chỉ
500 mA và phải kiểm trước.

## Trước khi cấp nguồn — phải tự đo

**Mức logic UART của A7680C.** ESP32 xuất 3.3 V; UART họ SIMCom A76xx thường là
1.8 V. Cấp nguồn module rời, đo chân TXD lúc rảnh: ~3.3 V nối thẳng được;
~1.8 V thì chừa trống hai chân RXD/TXD khi hàn và đấu qua module dịch mức 2
chiều (TXS0102 hoặc 2×BSS138 + trở kéo). Chân U4 là lỗ xuyên dùng header nên
không phải làm lại board.

## Trước khi đặt board

In `manufacturing/CHECK-1to1-footprints.pdf` ở **100 %** (tắt "fit to page"),
đặt U1–U4 thật lên giấy đối chiếu khoảng cách chân. Footprint U3 (KS0319) và
U4 (TDM-4G-V1) vẽ theo kích thước danh nghĩa, chưa đo trên hàng thật.

## Cấp nguồn

`J1` = 5 V/1 A (ESP32), `J2` = 5 V/2.5 A (SIM). **Cấp riêng.** Đừng câu J2 ăn
theo cọc của J1 — đường `+5V` chỉ 1.0 mm, xung 2 A của modem sẽ kéo sụt rail
ESP32. Một nguồn 5 V ≥ 3 A thì kéo hai cặp dây riêng, đấu hình sao tại nguồn.

## Ghi chú giá

`DFM-001`: board 105 × 82 mm **vượt ngưỡng 100 × 100 mm** của bậc giá rẻ nhất
tại JLCPCB/PCBWay. Thu chiều rộng xuống ≤ 100 mm sẽ rẻ hơn đáng kể, nhưng phải
bố trí lại linh kiện — chưa làm.

## Giới hạn của review

Không có thư mục `datasheets/`, không có MPN (0/8), không có API key và không có
SPICE simulator trên máy. Mọi kết luận về chân và điện là **kiểm tra tính nhất
quán**, không phải xác minh theo datasheet nhà sản xuất.

Báo cáo review đầy đủ: https://claude.ai/code/artifact/87d22087-bd5d-4769-baa9-9593b283e771

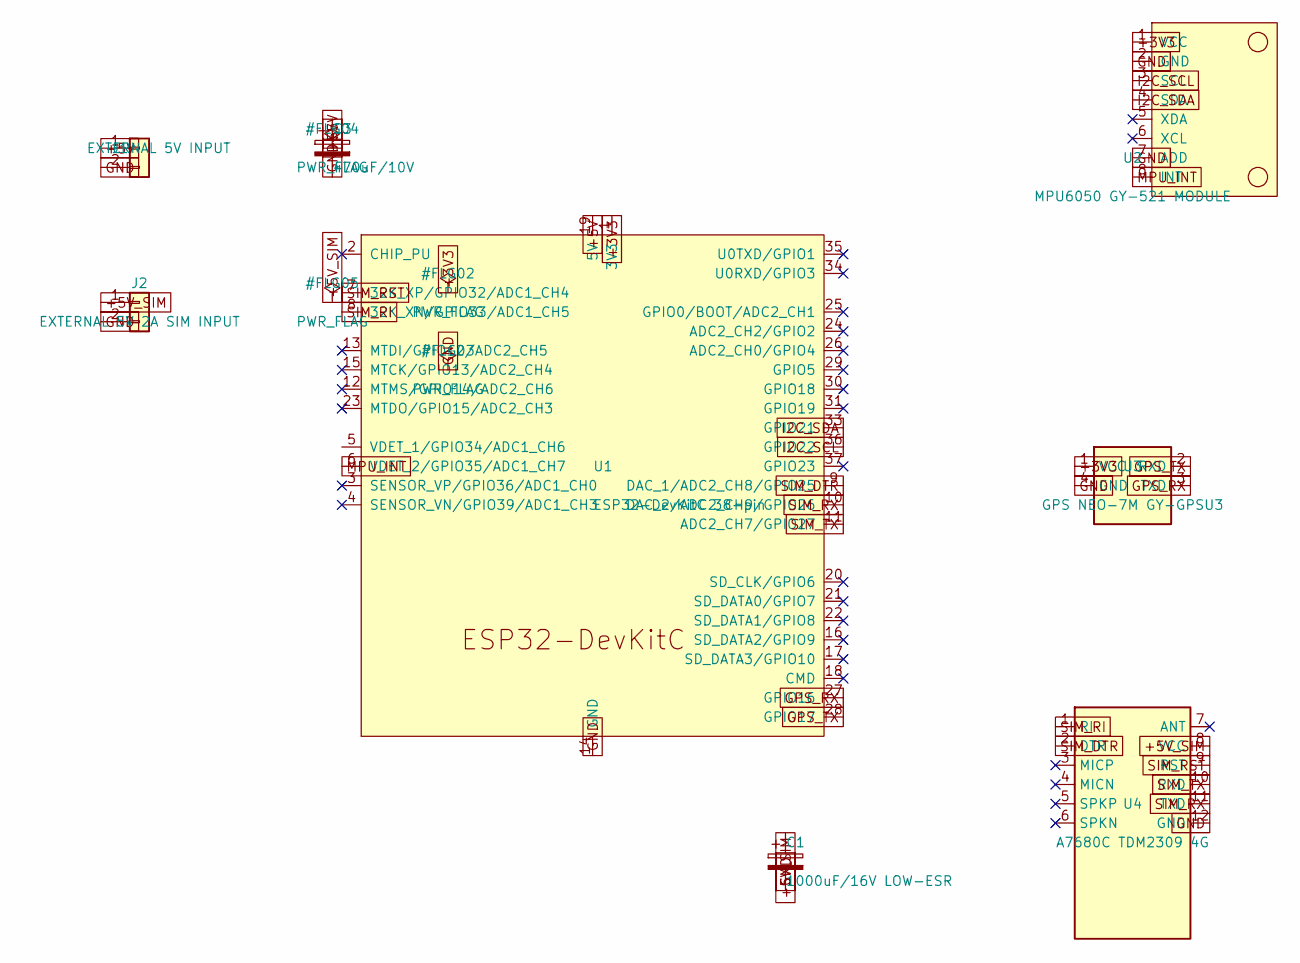
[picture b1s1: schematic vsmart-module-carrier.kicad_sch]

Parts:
C1: 1000uF/16V LOW-ESR; CP_Radial_D10.0mm_P5.00mm
C3: 470uF/10V; CP_Radial_D8.0mm_P3.50mm
J1: EXTERNAL 5V INPUT; SolderWire-1sqmm_1x02_P5.4mm_D1.4mm_OD2.7mm
J2: EXTERNAL 5V 2A SIM INPUT; SolderWire-1sqmm_1x02_P5.4mm_D1.4mm_OD2.7mm
U1: ESP32-DevKitC 38-pin; ESP32-DevKitC
U2: MPU6050 GY-521 MODULE; module_mpu6050
U3: GPS NEO-7M GY-GPSU3; GY-GPSU3-NEO7M
U4: A7680C TDM2309 4G; TDM-4G-V1

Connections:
+3V3: U1.1 (3V3), U2.1 (VCC), U3.1 (VCC)
+5V: C3.1, J1.1, U1.19 (5V)
+5V_SIM: C1.1, J2.1, U4.8 (VCC)
GND: C1.2, C3.2, J1.2, J2.2, U1.14 (GND), U1.32 (GND), U1.38 (GND), U2.2 (GND), U2.7 (ADD), U3.4 (GND), U4.12 (GND)
GPS_RX: U1.27 (GPIO16), U3.3 (TXD)
GPS_TX: U1.28 (GPIO17), U3.2 (RXD)
I2C_SCL: U1.36 (GPIO22), U2.3 (SCL)
I2C_SDA: U1.33 (GPIO21), U2.4 (SDA)
MPU_INT: U1.6 (VDET_2/GPIO35/ADC1_CH7), U2.8 (INT)
SIM_DTR: U1.9 (DAC_1/ADC2_CH8/GPIO25), U4.2 (DTR)
SIM_RI: U1.8 (32K_XN/GPIO33/ADC1_CH5), U4.1 (RI)
SIM_RST: U1.7 (32K_XP/GPIO32/ADC1_CH4), U4.9 (RST)
SIM_RX: U1.10 (DAC_2/ADC2_CH9/GPIO26), U4.11 (TXD)
SIM_TX: U1.11 (ADC2_CH7/GPIO27), U4.10 (RXD)

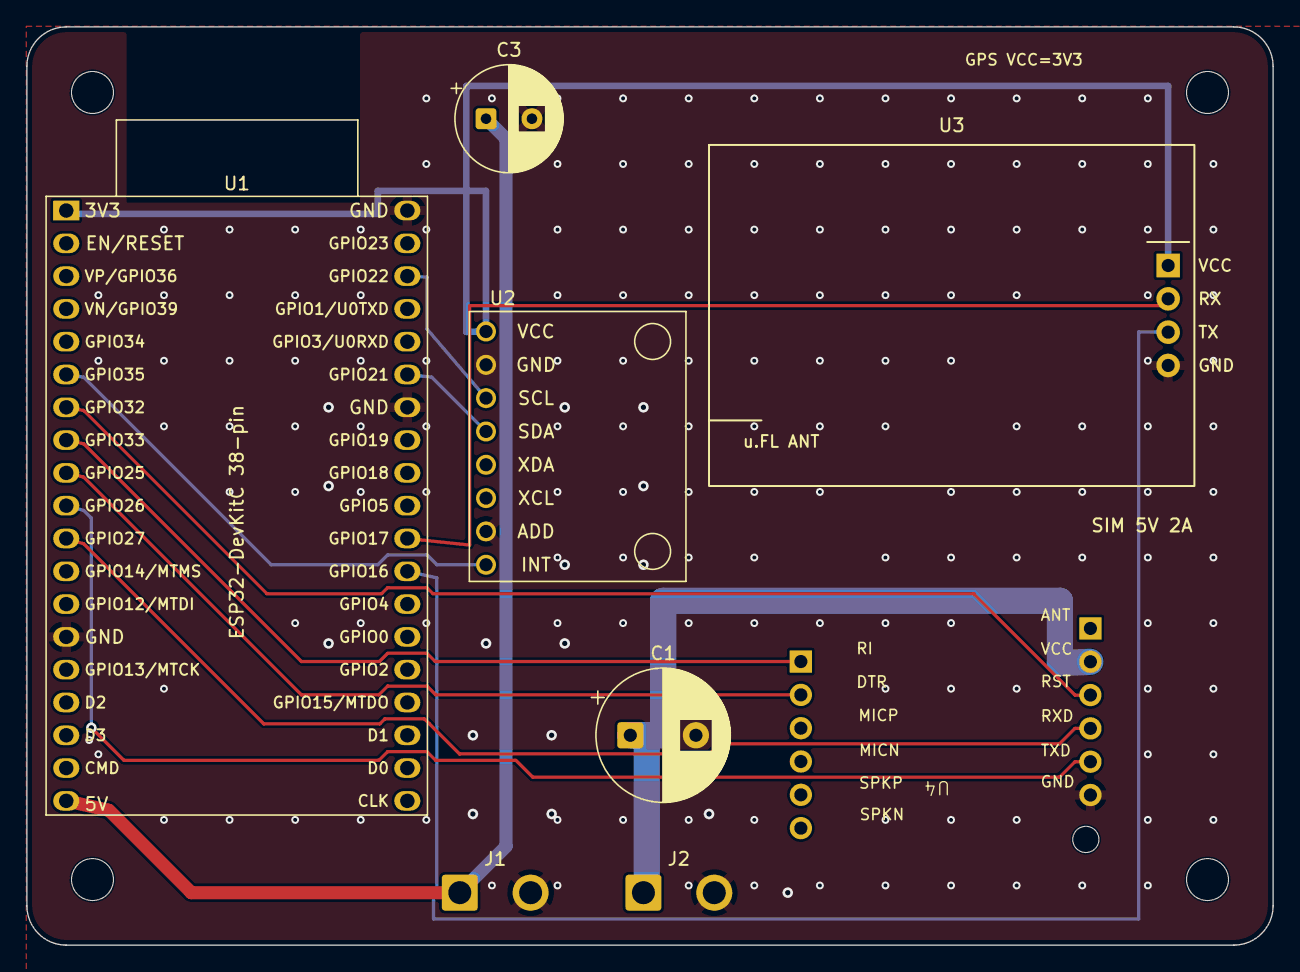
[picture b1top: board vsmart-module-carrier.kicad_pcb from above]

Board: 2 copper layers, 95.0 x 70.0 mm, 12 parts (0 on the bottom side), 14 nets.

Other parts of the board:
MH1, MH2, MH3, MH4: MountingHole_3.2mm_M3

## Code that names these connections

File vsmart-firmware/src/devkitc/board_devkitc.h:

// board_devkitc.h — Netlist record for the ESP32-DevKitC carrier, Rev C.
//
// Source of truth: vsmart-module-esp32/vsmart-module-carrier.kicad_pcb
//                  (Rev C, 2026-08-30, 105.1 × 82.1 mm, 2 layers)
//
// Net names on the schematic are **from the ESP32's point of view**:
//   GPS_TX = ESP32 transmits -> RXD of the GPS module
//   GPS_RX = ESP32 receives  <- TXD of the GPS module
// Same for SIM_TX / SIM_RX with the A7680C. Do not swap them.
//
// "U1 pin" is the pin number in the KiCad symbol; "silk" is what is printed on
// the DevKitC itself.
#pragma once
#include <Arduino.h>

namespace devkitc {

constexpr const char* NAME = "vsmart-carrier-revC (ESP32-DevKitC)";

// ── U3 · GPS NEO-7M (GY-GPSU3), UART2 ───────────────────────────────────────
// Rev C routes these as copper traces. The overrides exist only for bench
// bring-up, when the GPS is on jumper wires and you want to rule out a dead
// GPIO. Build them from platformio.ini, e.g.
//     build_flags = ${env.build_flags} -DGPS_RX_PIN=18 -DGPS_TX_PIN=19
// so the netlist record below stays true to the board.
//
// Do NOT pick GPIO1 or GPIO3. They are UART0, wired to the USB-serial bridge
// on the DevKitC module itself: the bridge and the GPS would both drive the
// same line, and flashing and the console would stop working.
// GPIO6-11 are the internal flash. GPIO12 must stay low at boot.
// Free and safe on this board: 18, 19, 23, 4, 13, 14 — plus 34/35/36/39 for RX
// only (those are input-only, which is all an RX pin has to be).
#ifndef GPS_RX_PIN
#define GPS_RX_PIN 16               // U1.27 GPIO16, silk "16"  <- U3.3 TXD  (net GPS_RX)
#endif
#ifndef GPS_TX_PIN
#define GPS_TX_PIN 17               // U1.28 GPIO17, silk "17"  -> U3.2 RXD  (net GPS_TX)
#endif
constexpr int8_t   GPS_RX   = GPS_RX_PIN;
constexpr int8_t   GPS_TX   = GPS_TX_PIN;
constexpr uint8_t  GPS_UART = 2;
// Starting point for the auto-probe in lib/Gps, not a hard setting.
// NEO-6M/7M/8M leave the factory at 9600; the M10 generation at 38400.
// Set this to whatever module is actually fitted and the probe locks on the
// first try; get it wrong and it costs 3 s per wrong candidate.
constexpr uint32_t GPS_BAUD = 9600;

// The GY-GPSU3 has no PPS pin — net GPS_PPS was dropped in Rev C, so U1.5
// (GPIO34) is unconnected and marked no-connect on the schematic.

// ── U4 · A7680C TDM2309 LTE, UART1 ──────────────────────────────────────────
constexpr int8_t   SIM_RX   = 26;   // U1.10 GPIO26, silk "26"  <- U4.11 TXD
constexpr int8_t   SIM_TX   = 27;   // U1.11 GPIO27, silk "27"  -> U4.10 RXD
constexpr int8_t   SIM_RST  = 32;   // U1.7  GPIO32, silk "32"  -> U4.9  RST (active LOW)
constexpr int8_t   SIM_DTR  = 25;   // U1.9  GPIO25, silk "25"  -> U4.2  DTR
constexpr int8_t   SIM_RI   = 33;   // U1.8  GPIO33, silk "33"  <- U4.1  RI  (active LOW)
constexpr uint8_t  SIM_UART = 1;
constexpr uint32_t SIM_BAUD = 115200;   // the A7680C autobauds; the first AT locks it in

// ── U2 · MPU6050 GY-521, I2C ────────────────────────────────────────────────
constexpr int8_t  I2C_SDA = 21;     // U1.33 GPIO21, silk "21"  <-> U2.4 SDA
constexpr int8_t  I2C_SCL = 22;     // U1.36 GPIO22, silk "22"  <-> U2.3 SCL
constexpr int8_t  MPU_INT = 35;     // U1.6  GPIO35, silk "35"  <-  U2.8 INT

// GPIO35 is INPUT-ONLY and has no internal pull resistors, so the pin must stay
// bare and the MPU6050 INT output has to be driven push-pull active-high.
constexpr uint8_t MPU_INT_PINMODE = INPUT;

// U2.7 (AD0) is tied to GND -> fixed address 0x68.
constexpr uint8_t MPU_ADDR = 0x68;

// ── Power (no firmware handles required) ────────────────────────────────────
// +5V     : J1 (5 V/1 A)   -> C3 470 µF/10 V   -> U1.19, trace 1.0 mm
// +5V_SIM : J2 (5 V/2.5 A) -> C1 1000 µF/16 V  -> U4.8,  trace 2.0 mm
// +3V3    : U1.1, output of the DevKitC's AMS1117 LDO -> U2.1 and U3.1
// Feed J1 and J2 separately: the 1.0 mm +5V trace sags under the modem's 2 A
// transmit burst if both share a terminal.

}  // namespace devkitc
